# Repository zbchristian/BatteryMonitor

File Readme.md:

Battery Monitor with low energy Bluetooth readout
=================================================
Measure and display the 
- capacity in Ampere hours (Ah) of a battery
- the voltage of the battery (V)
- the current flowing from/to the battery (A)

of a camper/mobil home 12V battery on an Android Smartphone.

The monitor is based on three modules (DC-DC converter, ESP32, ADS1115), which are placed either on a bread board or a PCB. 
The schematic and the layout of this base board can be found in the Eagle folder.

Depending on the used firmware, the device pulls about 10mA (25mA) from the 12V battery. An additional 8-9mA are drawn by the Hall current sensor.

Hardware
========
* ESP32 board (Mini)
* Current sensor (Hall sensor to measure the magnetic field, or shunt resistor) 
* Step-down regulator (DC-DC Buck converter)
  * Input: 10V-20V
  * Output: 5.8V (adjustable version)
  * Max. current: 1A
* ADS1115 16 bit ADC

The 5.8V output voltage of the DC-DC converter is due to the fact, that the current sensor (Hall sensor) and the ADC require very stable 5V. 
This is provided by the 5V regulator MCP1702/1703. The ESP32 module has its own 3.3V regulator and can handle up to 6V on the Vcc pin. 

For a version utilizing the internal ADC, see the [Readme](Readme_internalADC.md).

Current Sensor
==============
A split core current sensor with a Hall sensor or a shunt resistor is used to measure the current.

Hall Sensor
-----------
Advantage: sensor works contactless. No need to mess with the cabling, since the sensor is just placed around one of the battery cables.

Utilized model: YHDC HSTS016L +-20A
- 2.5+-0.625V 
- reference voltage 2.5V

Shunt Resistor
--------------
A commercial shunt suitable for a high current (e.g. 100A) is placed into the ground connection to the battery. The voltage drop is small (e.g. 70mV for 100A).
The ADS1115 allows to change the voltage range down to +-256mV. This makes it suitable to measure the current with sufficient precision, without the need of an additional amplifier.

The reached resolution is for both cases about 50mA.

Analog to digital conversion
============================
The ADC ADS1115 with 16 bit resolution is readily available as a module. It exhibits 4 channels, a wide adjustable voltage range, a build in amplifier and can directly measure voltage differences.  

Android APP
===========
Developed with the MIT App-Inventor2
- Low energy bluetooth (BLE) connection to the ESP32
- Main Screen with current, voltage, capacity
- Settings window 

Software
========
The Arduino IDE is used for the code development. 
Three different versions of the ESP32 firmware exist:
- Utilize the internal ADC ([code](./BatteryMonitor_internal_ADC/BatteryMonitor_internal_ADC.ino))
- Utilize an ADS1115 external ADC ([code](./BatteryMonitor_ADS1115/BatteryMonitor_ADS1115.ino))
- UTilize an ADS1115 external ADC and reduce the power by going into the light sleep mode of the ESP32 The ([code](./BatteryMonitor_lowpower/BatteryMonitor_lowpower.ino))

Requires packages
-----------------
- ESP32 support with BLE and Wire
- ADS1115_WE by Wolfgang Ewald

Concept
-------
- Settings: define time intervals and used channels in the `#define` section of the code
- Setup: reduce CPU clock to save power, setup timers and the external ADC
- Loop: Read the battery voltage and current, calculate the Ah and power and store current battery state to flash
- The BLE connection is initialized by the phone
- A sign-on message is expected by the ESP32. This is a hash value of the current time (salt) and a pre-shared pass phrase. 
- If the message is not received, the BLE connection is terminated.
- For the first 60 seconds the connection is possible without the passphrase
- Data are send to the APP every second as a block of 20 bytes. The values are 16 bit integer values, which have been scaled to reflect the predefined number of significant digits. 

The versions differ mainly in the way the timing is handled. 

The first two versions utilize a 1msec timer interrupt to define time intervals and trigger time dependent 
actions (reading the voltage/current value, calculate battery capacity, transmit via BT). 

The third version handles the timing once per loop() iteration: 
- the loop is running once every 100msec
- the corresponding delay is done either as a standard delay (BT activated) or by the ´light sleep´ mode (BT off) of the ESP32. 
These states are alternating with 5sec BT off and 1sec BT on until a phone connects.
- while BT is off, the CPU frequency is reduced from 80 Mhz down to 20 MHz, which saves an additional 3-4mA @ 12V

In total this reduces the required current from about 25mA down to approx 4mA @ 12V, when the device is in idle mode (BT off). 

Status Printout of the Device
-----------------------------
An USB connection to the ESP32 allows to view the status print out of the device. Connect a terminal program to the corresponding virtual serial port (e.g. COM port).
The measured values and status infomrmations are printed to the terminal and allow to perform the calibration of the sensors.  

Calibration
===========
The calibration of the battery voltage and current measurement is required.

Battery Voltage
---------------
The measured voltage might vary due to resistor variations. The default voltage divider reduces the voltage by a factor of 0.25 ( 10k/(10k+30k) ). 
This factor is defined as `R12V`.
In addition a small voltage offset might be present. This should be measured with a good voltage meter and the corrections entered into the source code 
function `Vcal12`.

Current Sensor
--------------
A Hall sensor contains active components and the voltage to current conversion should be checked. An voltage offset leads to a none zero current displayed for 0 Amps.
The printout messages on a connected terminal allows to compare the measured values with the applied voltage/current. Enter the corrected values into the functions `VcalSensor` and `V2Amps`. 
Non linear dependencies might be entered into the latter function as well. 

Misc
====
On the PCB three additional IO pins are available on pin headers (IO2, IO4, IO5). These are not yet utilized and can be used to attach more hardware. The pin header for 
IO5 provides in addition 3.3V, which can be used to connect an active touch button (e.g. based on the TTP223 chip).

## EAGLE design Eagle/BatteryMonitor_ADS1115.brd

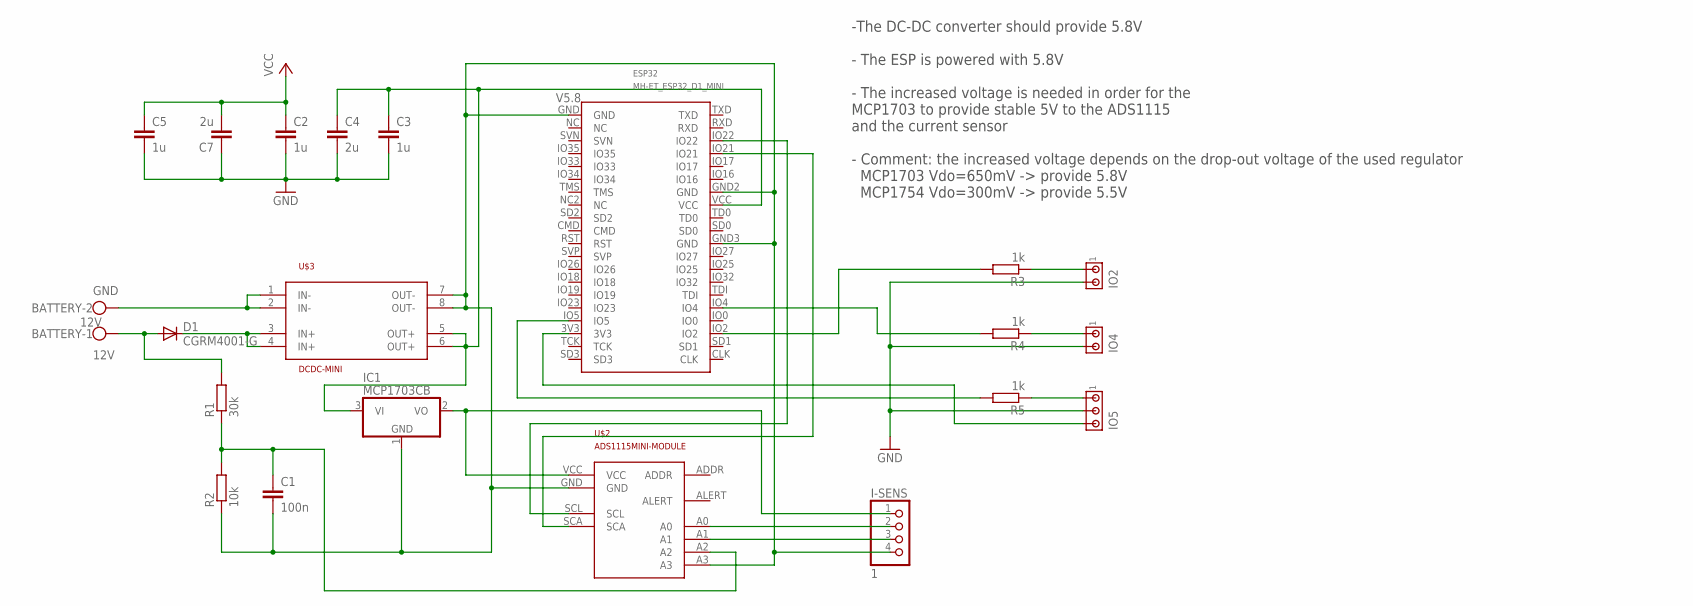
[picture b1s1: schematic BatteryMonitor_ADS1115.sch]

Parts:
BATTERY: 12V; W237-102
C1: 100n; C1206
C2, C3, C5: 1u; C1206
C4, C7: 2u; C1206
D1: CGRM4001-G; SOD-123_MINI-SMA
ESP32: MH-ET_ESP32_D1_MINI
I-SENS: 1; 1X04/90
IC1: MCP1703CB; SOT23
IO2, IO4: MTA02-100; 10X02MTA
IO5: MTA03-100; 10X03MTA
R1: 30k; R1206
R2: 10k; R1206
R3, R4, R5: 1k; R1206
U$2: ADS1115MINI-MODULE; ADS1115
U$3: DCDC-MINI

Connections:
12V: BATTERY.1, D1.A, R1.2
GND: BATTERY.2, C1.2, C2.2, C3.2, C4.2, C5.2, C7.1, ESP32.GND, ESP32.GND2 (GND), ESP32.GND3 (GND), I-SENS.4, IC1.1 (GND), IO2.2, IO4.2, IO5.2, R2.1, U$2.A3, U$2.GND, U$3.1 (IN-), U$3.2 (IN-), U$3.7 (OUT-), U$3.8 (OUT-)
unnamed: IO5.1, R5.1
unnamed: ESP32.IO2, R3.2
unnamed: ESP32.IO4, R4.2
unnamed: I-SENS.2, U$2.A0
unnamed: ESP32.IO5, R5.2
unnamed: I-SENS.3, U$2.A1
unnamed: ESP32.IO21, U$2.SCA
unnamed: ESP32.IO22, U$2.SCL
unnamed: C1.1, R1.1, R2.2, U$2.A2
unnamed: IO4.1, R4.1
unnamed: IO2.1, R3.1
unnamed: ESP32.3V3, IO5.3
V5.8: C3.1, C4.1, ESP32.VCC, IC1.3 (VI), U$3.5 (OUT+), U$3.6 (OUT+)
V12: D1.C, U$3.3 (IN+), U$3.4 (IN+)
VCC: C2.1, C5.1, C7.2, I-SENS.1, IC1.2 (VO), U$2.VCC

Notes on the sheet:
-The DC-DC converter should provide 5.8V - The ESP is powered with 5.8V - The increased voltage is needed in order for the MCP1703 to provide stable 5V to the ADS1115 and the current sensor - Comment: the increased voltage depends on the drop-out voltage of the used regulator MCP1703 Vdo=650mV -> p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

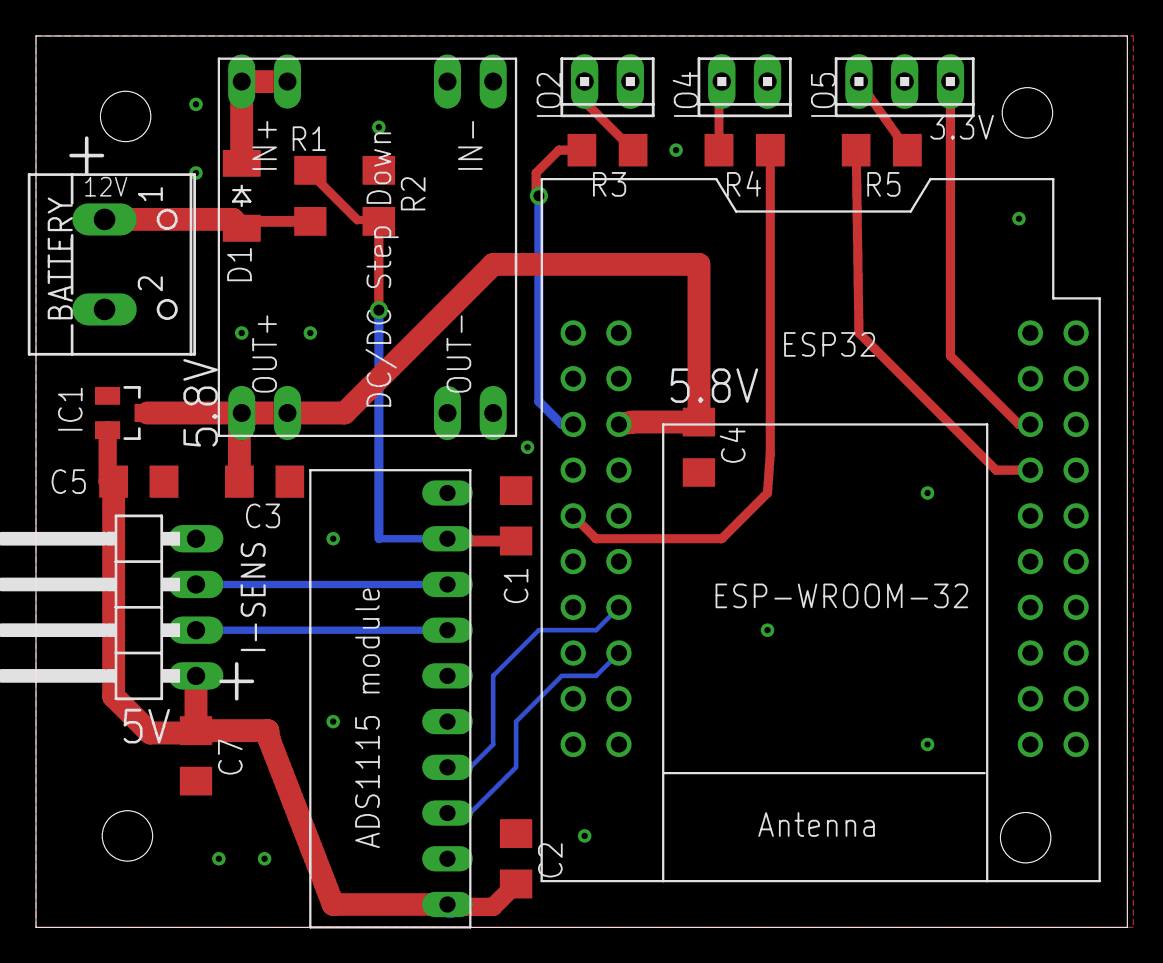
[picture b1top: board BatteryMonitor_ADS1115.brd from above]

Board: 2 copper layers, 60.6 x 49.5 mm, 21 parts (0 on the bottom side), 17 nets.

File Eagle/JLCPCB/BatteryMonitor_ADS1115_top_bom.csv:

Comment,Designator,Footprint,LCSC Part #
1k,R3 R4 R5,R1206,
1u,C2 C3 C5,C1206,
2u,C4 C7,C1206,
10k,R2,R1206,
33k,R1,R1206,
100n,C1,C1206,
CGRM4001-G,D1,SOD-123_MINI-SMA,
MCP1703CB,IC1,SOT23,

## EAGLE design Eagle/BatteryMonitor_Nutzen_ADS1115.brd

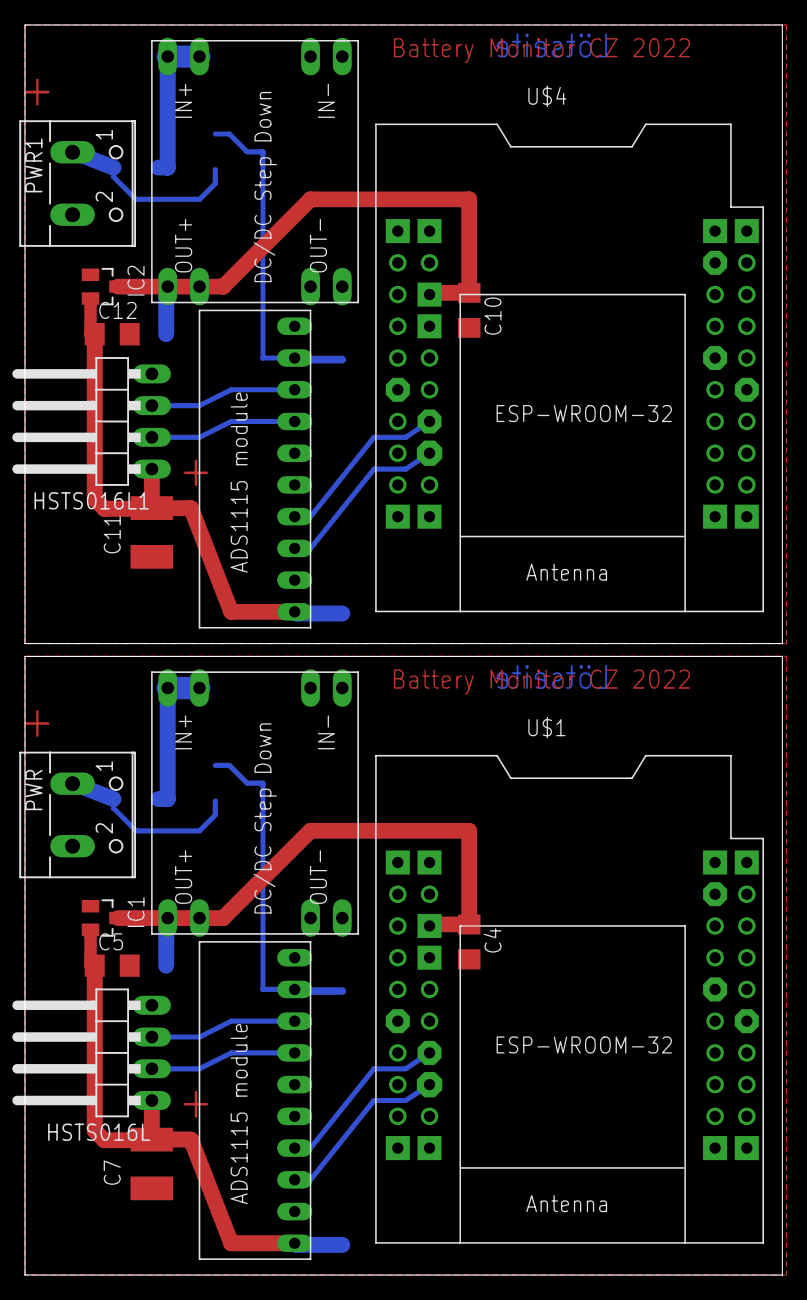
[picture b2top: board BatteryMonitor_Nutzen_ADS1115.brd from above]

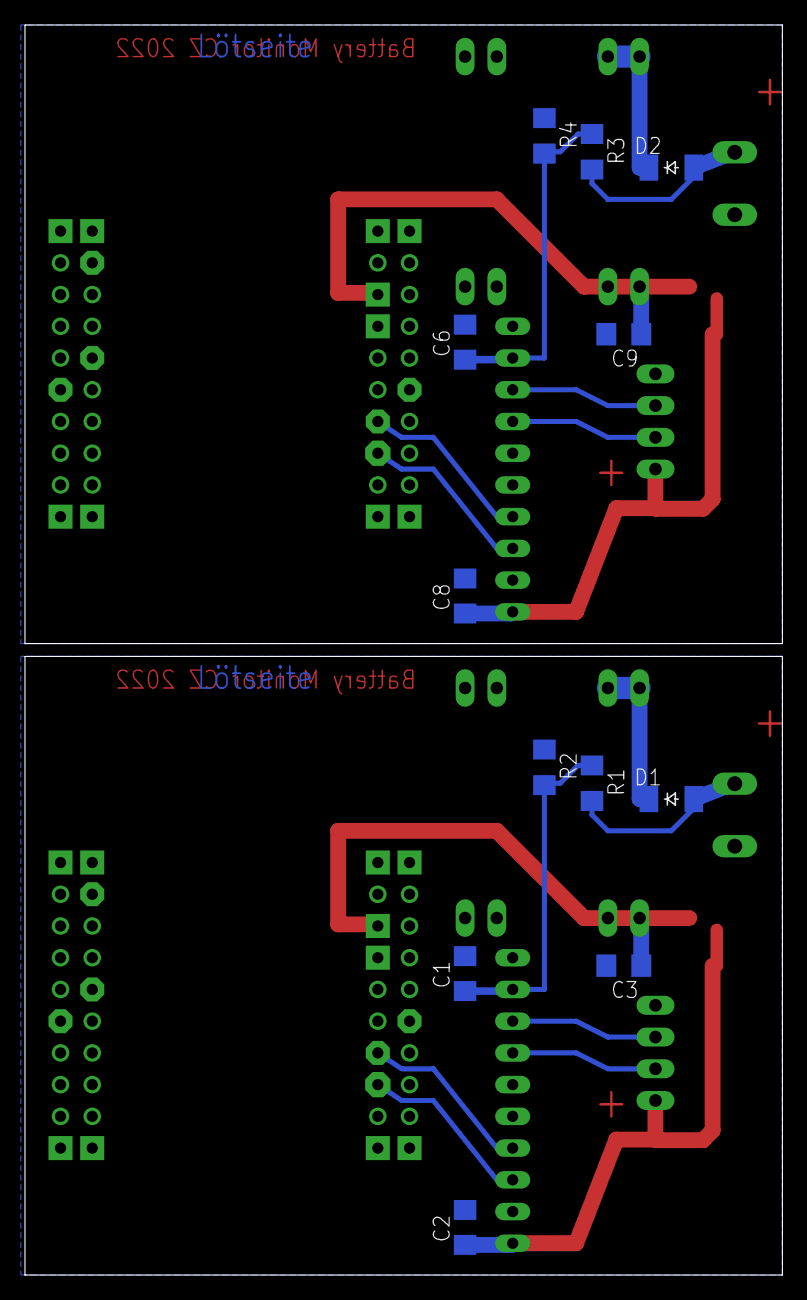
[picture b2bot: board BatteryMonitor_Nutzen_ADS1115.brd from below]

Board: 2 copper layers, 60.6 x 100.1 mm, 30 parts (12 on the bottom side), 20 nets.

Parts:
C1, C2, C3, C4, C5, C6, C8, C9, C10, C12: 100n; C1206
C7, C11: 100n; C4532
D1, D2: CGRM4001-G; SOD-123_MINI-SMA
HSTS016L, HSTS016L1: 1; 1X04/90
IC1, IC2: MCP1703CB; SOT23
PWR, PWR1: 12V; W237-102
R1, R3: 31k; R1206
R2, R4: 10k; R1206
U$1, U$4: MH-ET_ESP32_D1_MINI
U$2, U$5: ADS1115MINI-MODULE; ADS1115
U$3, U$6: DCDC-MINI

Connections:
GND: C1.2, C2.2, C3.2, C4.2, C5.2, C7.1, HSTS016L.4, IC1.1, PWR.2, R2.1, U$1.GND, U$1.GND2, U$1.GND3, U$2.A3, U$2.GND, U$3.1, U$3.2, U$3.7, U$3.8
GND1: C6.2, C8.2, C9.2, C10.2, C11.1, C12.2, HSTS016L1.4, IC2.1, PWR1.2, R4.1, U$4.GND, U$4.GND2, U$4.GND3, U$5.A3, U$5.GND, U$6.1, U$6.2, U$6.7, U$6.8
unnamed: D1.A, PWR.1, R1.2
unnamed: U$4.IO21, U$5.SCA
unnamed: U$4.IO22, U$5.SCL
unnamed: HSTS016L.2, U$2.A0
unnamed: HSTS016L1.2, U$5.A0
unnamed: HSTS016L.3, U$2.A1
unnamed: U$1.IO21, U$2.SCA
unnamed: U$1.IO22, U$2.SCL
unnamed: C1.1, R1.1, R2.2, U$2.A2
unnamed: HSTS016L1.3, U$5.A1
unnamed: C6.1, R3.1, R4.2, U$5.A2
unnamed: D2.A, PWR1.1, R3.2
V1: D2.C, U$6.3, U$6.4
V5.1: C9.1, C10.1, IC2.3, U$4.VCC, U$6.5, U$6.6
V5.5: C3.1, C4.1, IC1.3, U$1.VCC, U$3.5, U$3.6
V12: D1.C, U$3.3, U$3.4
VCC: C2.1, C5.1, C7.2, HSTS016L.1, IC1.2, U$2.VCC
VCC1: C8.1, C11.2, C12.1, HSTS016L1.1, IC2.2, U$5.VCC

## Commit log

2021-01-20 Bqttery Monitor based on ESP32 and BLE readout via MIT AppInventor APp
2021-01-22 Move ESp32 source into folder
2021-01-22 Add Readme.md
2021-01-22 Modified Readme.md
2021-01-31 Add images of prototype and App
2021-01-31 Resize images to width=300px
2021-02-27 Add Alert to display errors and progress Add procedure to receive history data. Not displayed yet
2023-01-31 ADS1115 as external ADC
2023-01-31 Optimize part placement
2023-01-31 Read and filter voltages from ADS1115
2023-02-02 Revert internal ADC version back to master
2023-02-02 Verbose print
2023-02-04 Update App for Android 12 and 13 and calibrate voltage and current
2023-02-04 Update blocks
2023-02-05 Add current measurement with a shunt resistor
2023-02-05 Update documentation
2023-02-05 New images with ADS1115
2023-02-05 Update Readme.md
    Replace images
2023-02-05 Update Readme.md
    Correct image
2023-02-05 Update Readme.md
    Correct images
2023-02-05 add 500px high images
2023-02-05 add text to images
2023-02-05 Move internal ADC Readme_internalADC.md
2023-02-07 Update docs
2023-02-07 Update doc
2023-02-07 And more docs
2023-12-08 Change layout - all SMD on top
2023-12-08 Remove temp file
2023-12-08 Correct description of DCDC output voltage
2023-12-09 Update layout: add 3.3V to IO connector
2023-12-23 Calibration done and documented
2023-12-29 Fix issue with BLE reconnect and changing the sign-on message
2024-01-01 Cleanup
2024-01-03 Add schematic as PDF
2024-01-20 Add low power version of the ESP32 firmware
2024-01-20 Update for the low power version
2024-01-20 Fix link and formatting
2024-01-21 correct time difference calculations and reduce CPU speed (BT off)
2024-01-21 Update docu
2024-01-22 Correct comments
2024-03-16 Fix negative current offset bug Allow in APP to set pass phrase if not connected
